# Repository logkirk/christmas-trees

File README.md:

# christmas-trees

Simple light-up Christmas tree ornaments.

This was a practice project for learning Altium Designer and practicing PCB design, board bring-up, and debugging.

## Design

The double-sided board uses the front silkscreen layer to make the LEDs appear like a strand of lights on a Christmas tree. When two CR2032 coin cell batteries are inserted on the back and the switch is turned on, the lights flash sequentially.

The design uses a simple LM555 timer circuit to increment an octal counter. Each output of the counter controls a single LED.

## Files

```
.
├── altium       original Altium Designer files
├── kicad        converted KiCad files
├── images       schematic, board view, and PCB images
└── README.md
```

## Project Images

### Schematic
<details>
<summary>Click to expand</summary>

</details>

### Board Views
<details>
<summary>Click to expand</summary>

</details>

### Bare Board

Bare board fresh from JLCPCB. They came back looking clean.

<details>
<summary>Click to expand</summary>

</details>

### Modded Board

Of course the first run had some bugs. I was able to get it working after a bit of troubleshooting and some board modifications.

<details>
<summary>Click to expand</summary>

</details>

## Lessons Learned

- Double check trace widths before ordering. I used the default trace width, which led to the traces being thinner than expected. It didn't cause any electrical issues, but the traces could've been wider for the same cost.

## Next Steps

- Translate indentified design issues back into schematic and layout
- Order another run of boards

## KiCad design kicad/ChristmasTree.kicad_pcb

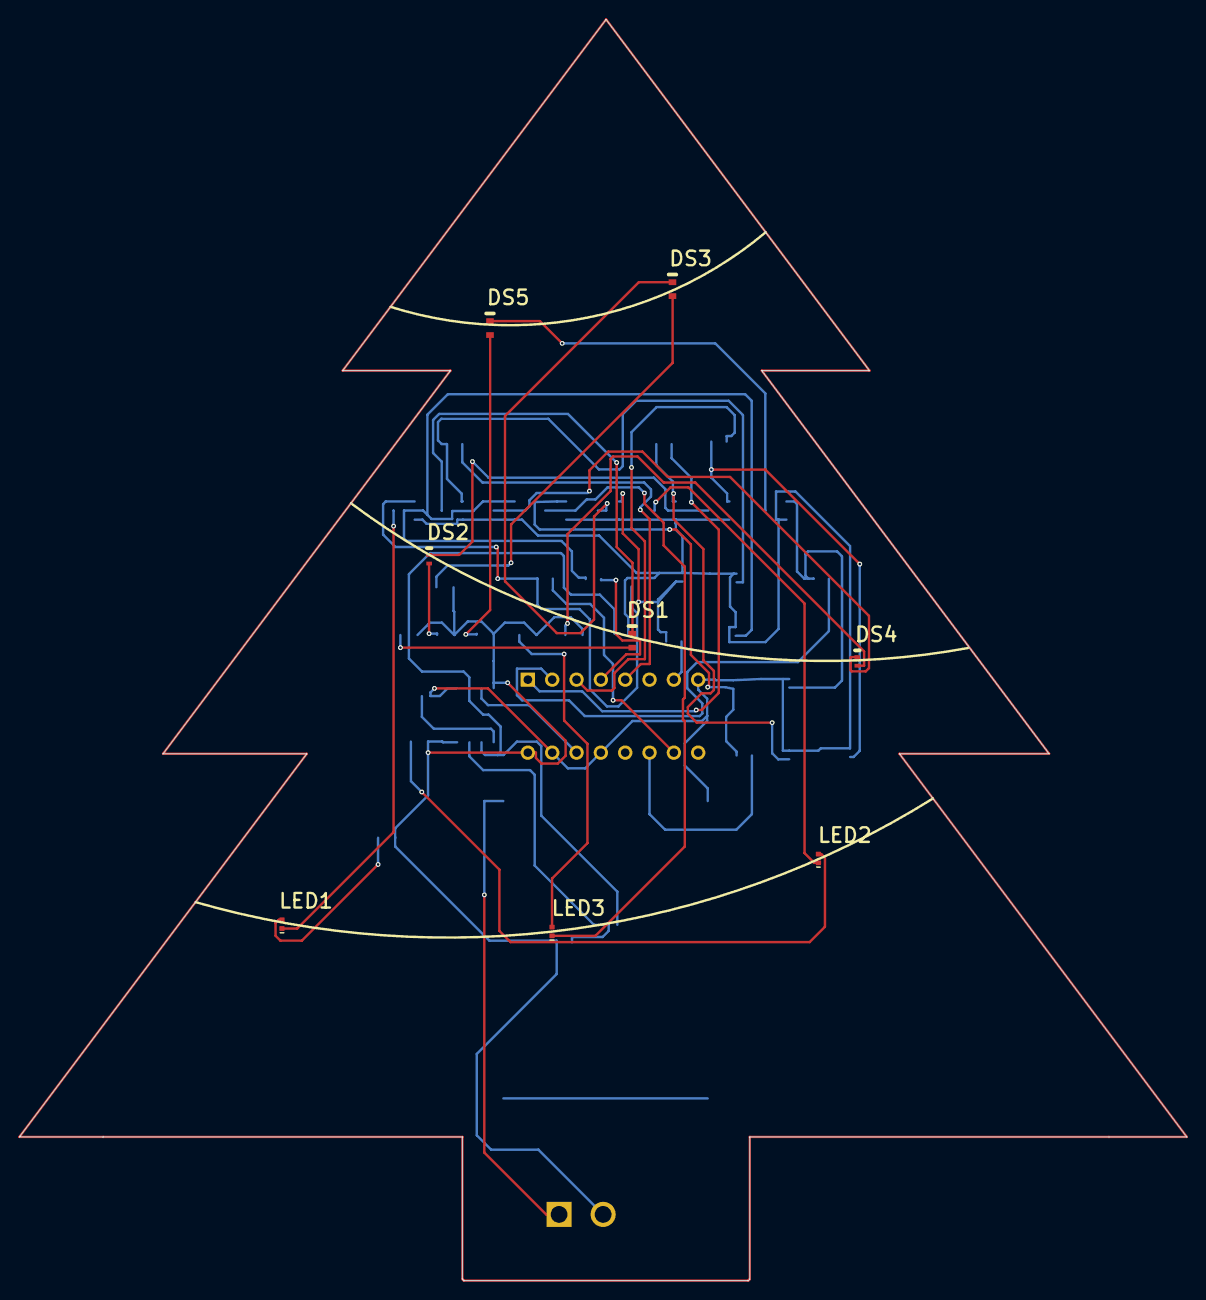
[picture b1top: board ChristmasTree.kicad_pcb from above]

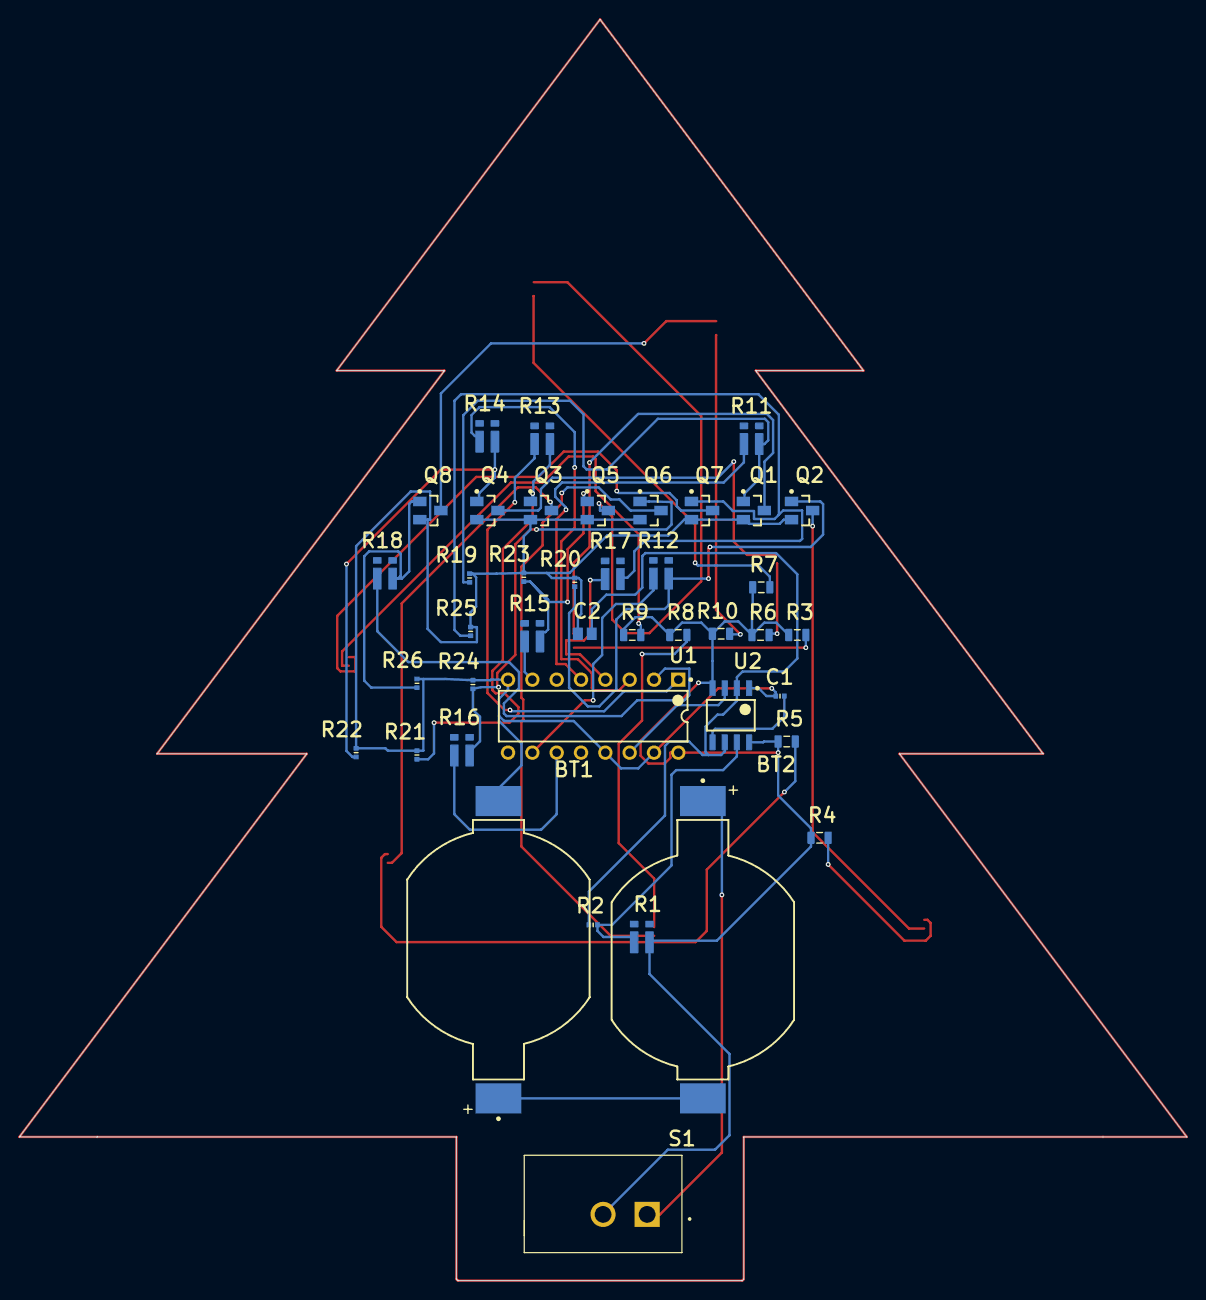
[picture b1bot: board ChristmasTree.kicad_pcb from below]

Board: 2 copper layers, 121.9 x 131.7 mm, 49 parts (41 on the bottom side), 40 nets.

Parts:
BT1, BT2: 796136-1; TECO-796136-1_V
C1: Capacitor 10nF +/-20% 50V 0402; CAPC0402(1005)60_L
C2: Capacitor 100 nF +/-10% 50 V 0805; CAPC2013X95X50LL10T25
DS1, DS3, DS5: TLMS1100-GS08; VISH-TLMX1100_V
DS2, DS4: 16-219A/T2D-AR2T1QY/3T; EVRL-0402-2_V
LED1, LED2, LED3: QBLP595-IG; QTB-QBLP595_V
Q1, Q2, Q3, Q4, Q5, Q6, Q7, Q8: BSS138; FAIR-SOT23-3_V
R1, R11, R12, R13, R14, R15, R16, R17, R18: KRL3216T4A-M-R007-F-T1; SUSUMU-3216T4A
R2: Resistor 1M +/-1 % 0402 63 mW; RESC0402(1005)_L
R3, R4, R5, R6, R7, R8, R9, R10: Resistor 470R +/-5% 0805 125 mW; RESC0805(2012)_L
R19, R20, R21, R22, R23, R24, R25, R26: 2D26MR2F; RESC0402(1005)_L
S1: GF-123-0054; SW_GF-123-0054
U1: CD4022BE; N0016A
U2: LM555CM/NOPB; D0008A_M

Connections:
GND: BT1.2, C1.1, C2.1, Q1.2, Q2.2, Q3.2, Q4.2, Q5.2, Q6.2, Q7.2, Q8.2, R19.2, R20.2, R21.2, R22.2, R23.2, R24.2, R25.2, R26.2, U1.8, U1.13, U1.15, U2.1
NetBT1_1: BT1.1, BT2.2
NetBT2_1: BT2.1, S1.1
NetC1_2: C1.2, U2.5
NetC2_2: C2.2, R2.1, U2.2, U2.6
NetDS1_1: DS1.1, R3.2
NetDS1_2: DS1.2, Q1.3
NetDS2_1: DS2.1, R6.2
NetDS2_2: DS2.2, Q4.3
NetDS3_1: DS3.1, R7.2
NetDS3_2: DS3.2, Q5.3
NetDS4_1: DS4.1, R9.2
NetDS4_2: DS4.2, Q7.3
NetDS5_1: DS5.1, R10.2
NetDS5_2: DS5.2, Q8.3
NetLED1_1: LED1.1, Q2.3
NetLED1_2: LED1.2, R4.2
NetLED2_1: LED2.1, Q3.3
NetLED2_2: LED2.2, R5.2
NetLED3_1: LED3.1, Q6.3
NetLED3_2: LED3.2, R8.2
NetQ1_1: Q1.1, R11.2, R19.1
NetQ2_1: Q2.1, R12.2, R20.1
NetQ3_1: Q3.1, R13.2, R21.1
NetQ4_1: Q4.1, R14.2, R22.1
NetQ5_1: Q5.1, R15.2, R23.1
NetQ6_1: Q6.1, R16.2, R24.1
NetQ7_1: Q7.1, R17.2, R25.1
NetQ8_1: Q8.1, R18.2, R26.1
NetR1_1: R1.1, R2.2, U2.7
NetR11_1: R11.1, U1.5
NetR12_1: R12.1, U1.10
NetR13_1: R13.1, U1.1
NetR14_1: R14.1, U1.3
NetR15_1: R15.1, U1.7
NetR16_1: R16.1, U1.11
NetR17_1: R17.1, U1.4
NetR18_1: R18.1, U1.2
NetU1_14: U1.14, U2.3
VCC: R1.2, R3.1, R4.1, R5.1, R6.1, R7.1, R8.1, R9.1, R10.1, S1.2, U1.16, U2.4, U2.8

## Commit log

2026-04-17 Added images and readme
2026-04-17 Made images expandable
